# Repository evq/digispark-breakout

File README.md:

# Digispark breakout

A digispark breakout primarily aimed at 3 pin "arduino" modules. I use it with
relay boards, DHT11 / DHT22 temperature / humidity sensors, and hall effect sensors.

Shared on [OSH Park.](https://oshpark.com/shared_projects/2PvuLxGp)

## Design notes

* Exposes two D/A pins (P5 and P2) and one PWM pin (P0), P3 and P4 are not
exposed as this is designed to primarily be used with
[Littlewire](https://github.com/littlewire/Little-Wire) over USB. 
* The center five pins are designed to allow three pin modules with any permutation of pins.
* V+ on the header is selectable via a jumper between Vin and 5V from the
regulator.

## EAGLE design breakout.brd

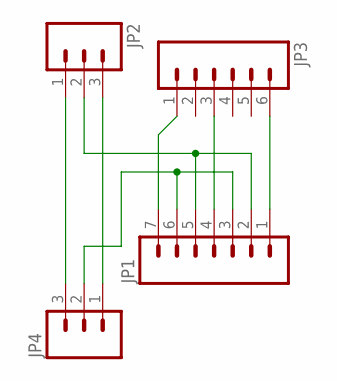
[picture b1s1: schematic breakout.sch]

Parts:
JP1: M07; 1X07
JP2, JP4: M03PTH; 1X03
JP3: M06SIP; 1X06

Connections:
unnamed: JP1.1, JP3.6
unnamed: JP1.4, JP3.3
unnamed: JP1.3, JP1.6, JP4.2
unnamed: JP2.3, JP4.1
unnamed: JP2.1, JP4.3
unnamed: JP1.2, JP1.5, JP2.2
unnamed: JP1.7, JP3.1

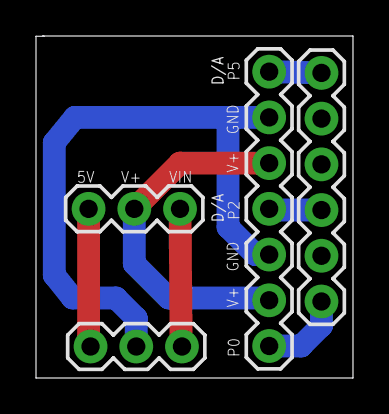
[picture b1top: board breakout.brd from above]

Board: 2 copper layers, 17.6 x 19.0 mm, 4 parts (0 on the bottom side), 7 nets.

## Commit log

2015-04-09 Initial commit, sent to oshpark
2015-04-13 Add link on OSH Park, and board previews

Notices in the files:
parts and their libraries:
SparkFun: Licensing: CC v3.0 Share-Alike You are welcome to use this library for commercial purposes.
SparkFun-Connectors: Licensing: Creative Commons ShareAlike 4.0 International - https://creativecommons.org/licenses/by-sa/4.0
